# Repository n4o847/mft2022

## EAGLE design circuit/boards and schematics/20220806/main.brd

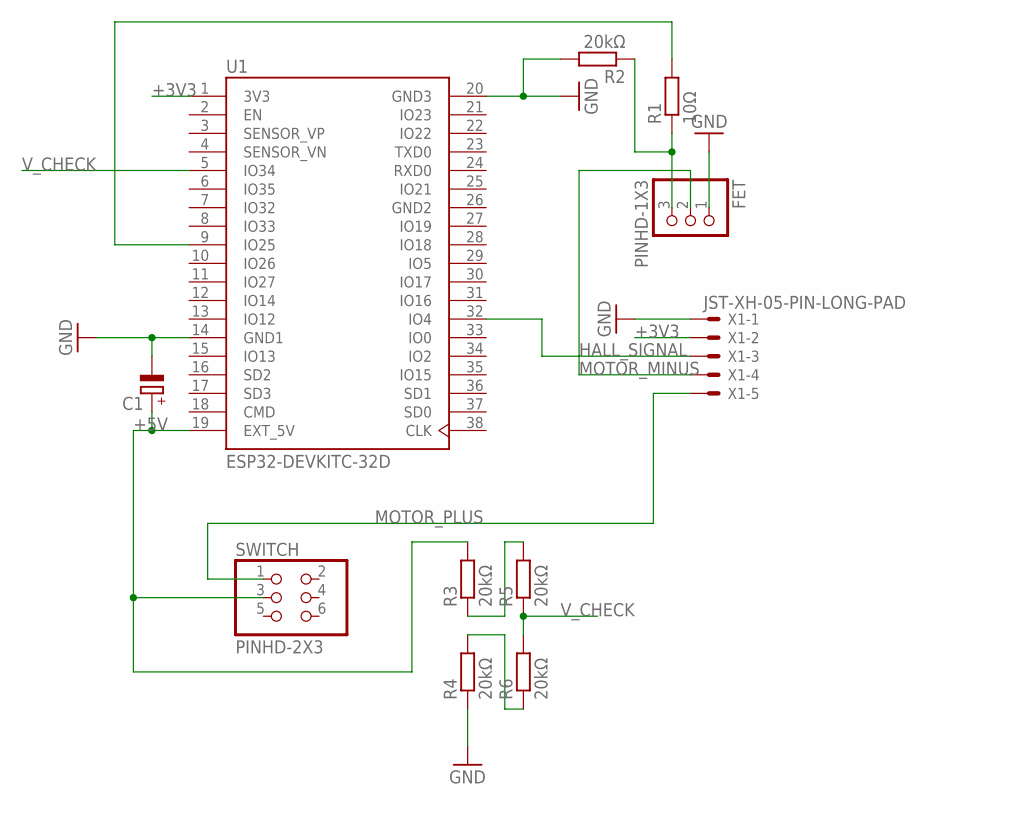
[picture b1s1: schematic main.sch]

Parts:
C1: CPOL-EUE5-10.5; E5-10,5
FET: PINHD-1X3; 1X03
R1: 10Ω; 0207/10
R2, R3, R4, R5, R6: 20kΩ; 0207/10
SWITCH: PINHD-2X3; 2X03
U1: ESP32-DEVKITC-32D; MODULE_ESP32-DEVKITC-32D
X1: JST-XH-05-PIN-LONG-PAD; JST-XH-05-PACKAGE-LONG-PAD

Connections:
+3V3: U1.1 (3V3), X1.2
+5V: C1.+, R3.2, SWITCH.3, U1.19 (EXT_5V)
GND: C1.-, FET.1, R2.2, R4.1, U1.14 (GND1), U1.20 (GND3), X1.1
GND2: U1.26 (GND2)
HALL_SIGNAL: U1.32 (IO4), X1.3
MOTOR_MINUS: FET.2, X1.4
MOTOR_PLUS: SWITCH.1, X1.5
unnamed: FET.3, R1.1, R2.1
unnamed: R1.2, U1.9 (IO25)
unnamed: R3.1, R5.2
unnamed: R4.2, R6.1
V_CHECK: R5.1, R6.2, U1.5 (IO34)

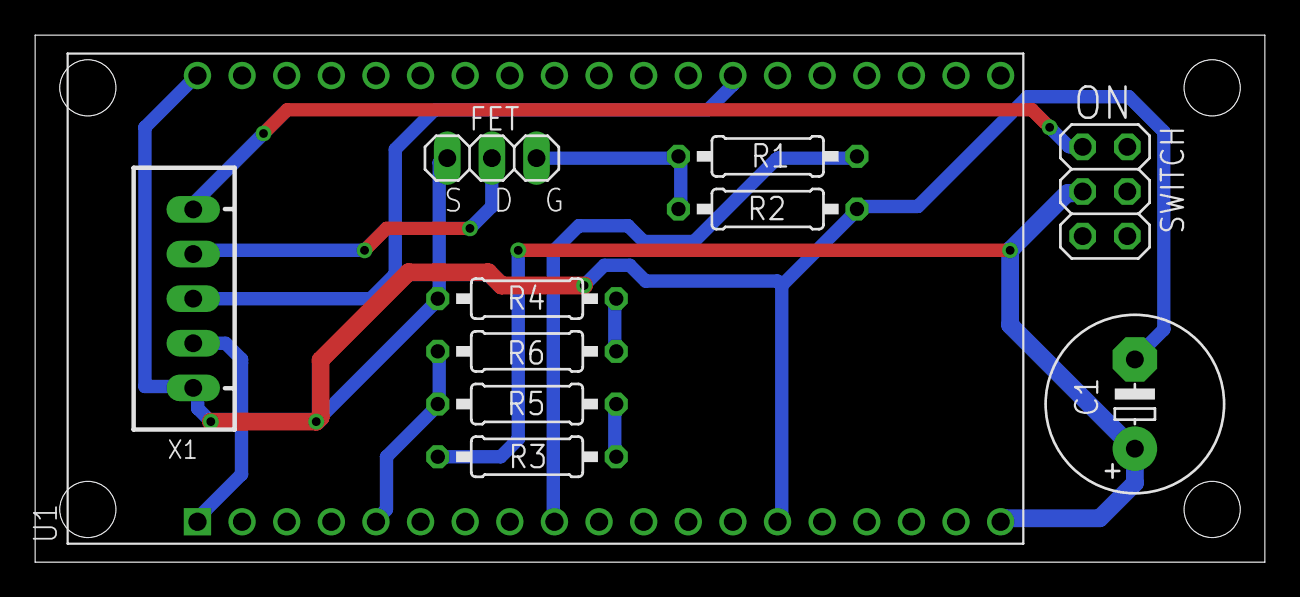
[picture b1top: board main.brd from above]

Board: 2 copper layers, 70.0 x 30.0 mm, 11 parts (0 on the bottom side), 11 nets.

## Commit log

2022-08-06 add board
2022-08-06 fix some lines
2022-08-06 change screw holes
2022-08-06 remove resistors
2022-08-06 created garber files
2022-08-07 added gerber files to order
2022-08-21 とりあえず train_esp32_simple をコピー
2022-08-21 バッテリーの電圧を測定（動作確認済み）
